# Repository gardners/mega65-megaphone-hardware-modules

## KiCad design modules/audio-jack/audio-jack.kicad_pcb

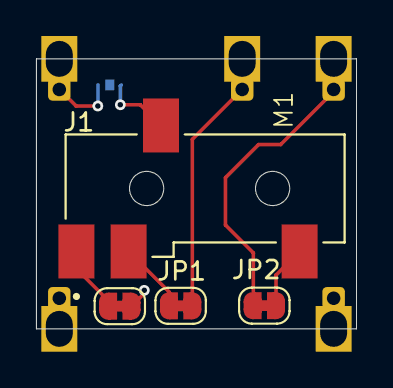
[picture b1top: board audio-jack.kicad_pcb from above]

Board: 2 copper layers, 17.8 x 15.0 mm, 6 parts (1 on the bottom side), 8 nets.

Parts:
J1: SJ-43514-SMT-TR; CUI_SJ-43514-SMT-TR
JP1, JP2, JP3, JP4: Jumper_2_Bridged; SolderJumper-2_P1.3mm_Bridged_RoundedPad1.0x1.5mm
M1: MegaCastle2x7-Module-I15.0x13.0-M8314-SPAREPAD

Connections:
GND: JP3.2 (B), M1.7 (GND)
LEFT: JP4.1 (A), M1.8
MIC: JP1.2 (B), M1.12
unnamed: J1.4, JP1.1 (A)
unnamed: J1.2, JP2.2 (B)
unnamed: J1.1, JP3.1 (A)
unnamed: J1.3, JP4.2 (B)
RIGHT: JP2.1 (A), M1.14

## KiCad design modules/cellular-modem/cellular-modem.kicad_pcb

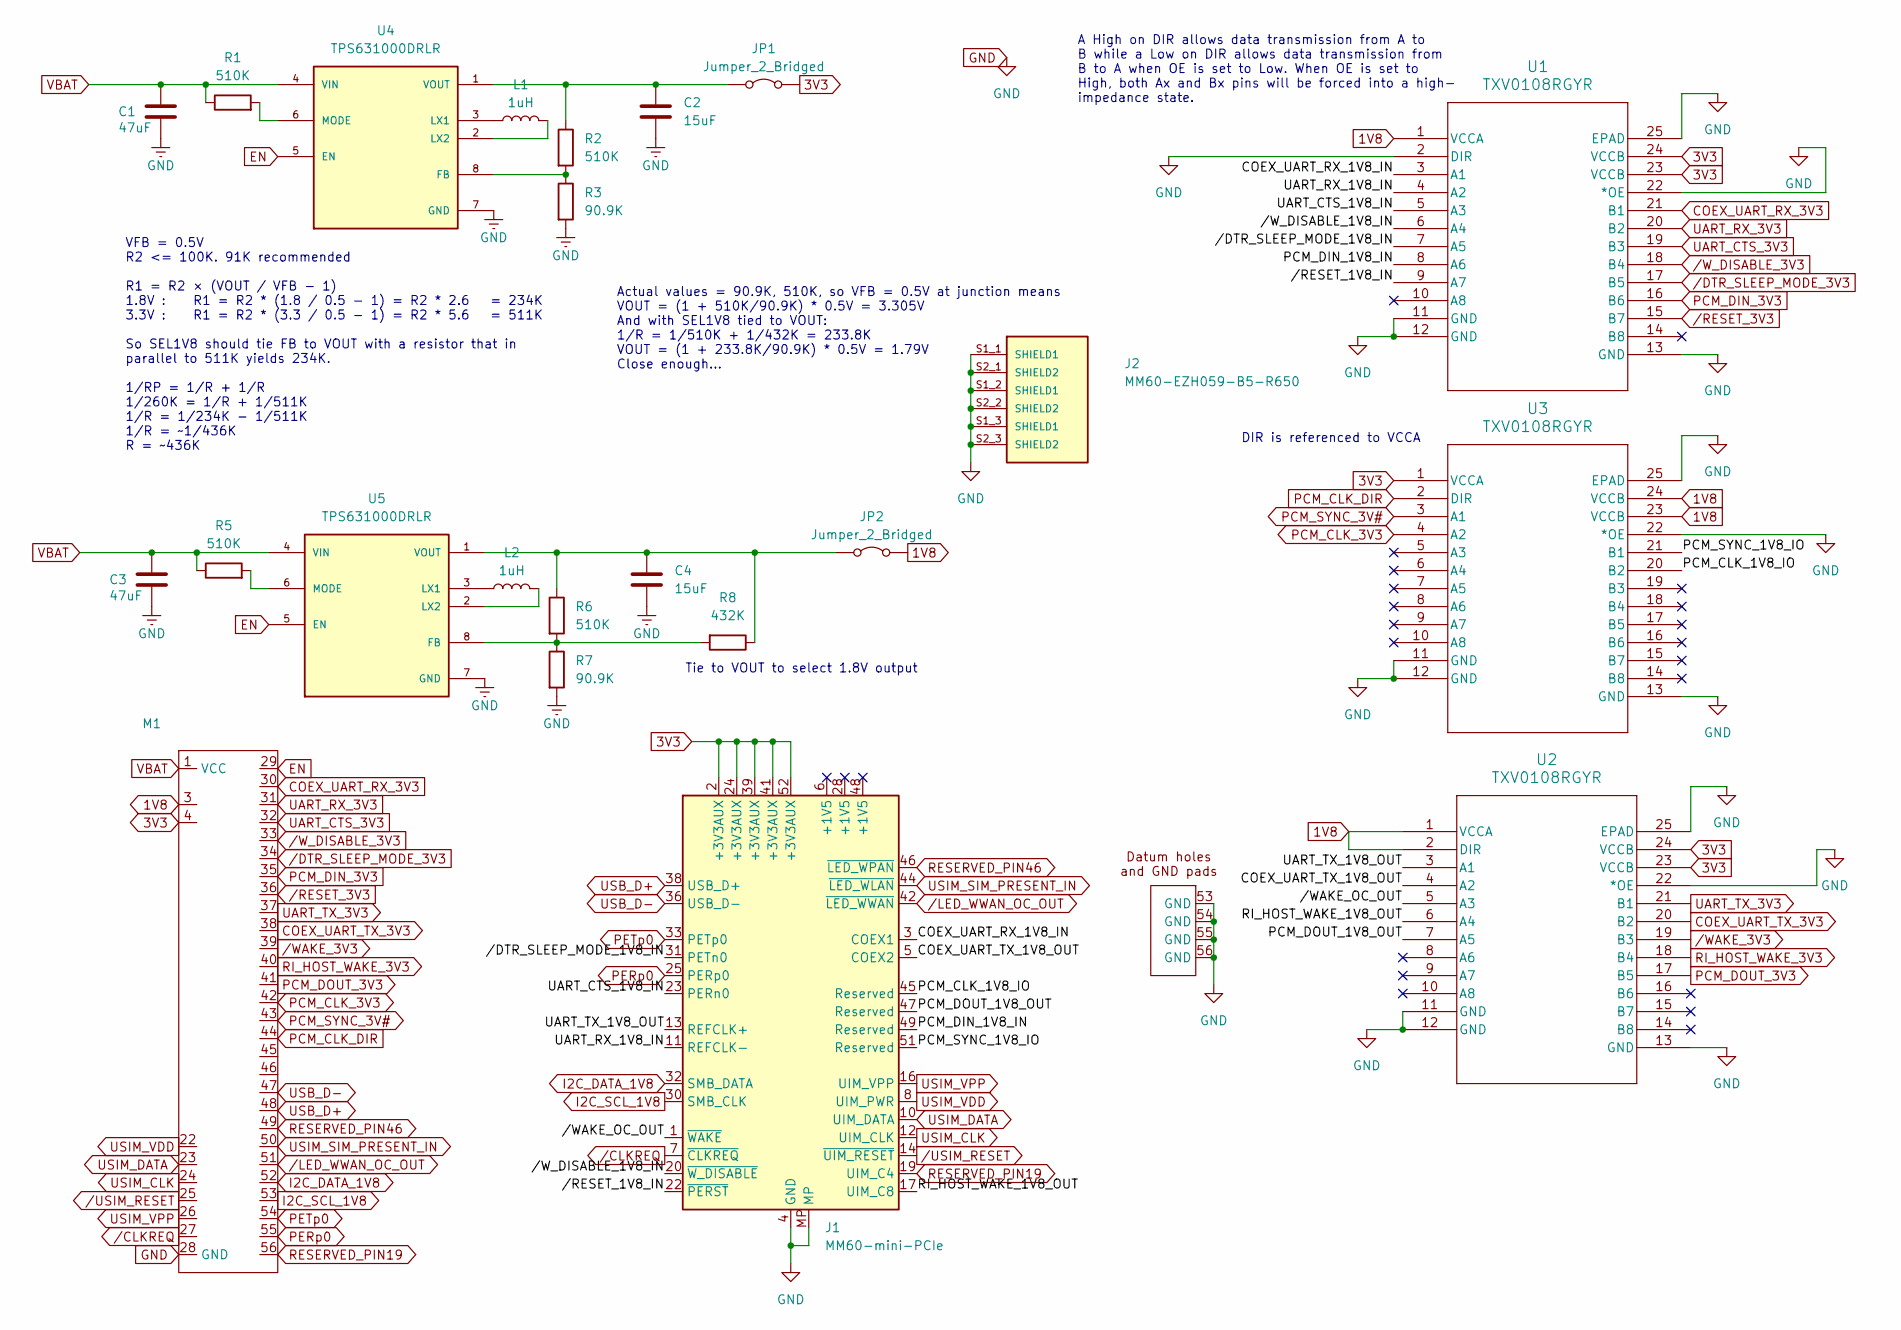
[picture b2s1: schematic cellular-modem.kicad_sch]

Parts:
C1: 47uF; C_0805_2012Metric; Mouser_PN GRM219R60J476ME44
C2, C4: 15uF; C_0805_2012Metric; Mfr. PN C2012X7S1A156M125AC; Mouser_PN 810-C2012X7S1A156M1C
C3: 47uF; C_0805_2012Metric; Mfr. PN GRM219R60J476ME44D; Mouser_PN GRM219R60J476ME44
J1: MM60-mini-PCIe; CONN_MM60-52B1-E1-R650_JAE; Mfr. PN MM60-52B1-G1-R850; Mouser_PN 656-MM6052B1G1R850
J2: MM60-EZH059-B5-R650; JAE_MM60-EZH059-B5-R650; PARTREV 3; Mouser_PN 656-MM60-EZH059-B5-R
JP1, JP2: Jumper_2_Bridged; SolderJumper-2_P1.3mm_Bridged2Bar_RoundedPad1.0x1.5mm
L1: 1uH; L_1008_2520Metric_Pad1.43x2.20mm_HandSolder; Mouser_PN 81-DFE252012P-1R0MP2
L2: 1uH; L_1008_2520Metric_Pad1.43x2.20mm_HandSolder; Mfr. PN DFE252012P-1R0M=P2; Mouser_PN 81-DFE252012P-1R0MP2
M1: MegaCastle2x28-Module-I42.8x66.3-MB00007FFFFFFFF-SPAREPAD
R1, R2, R5, R6: 510K; R_0805_2012Metric; Mouser_PN CR0805-JW-514ELF
R3, R7: 90.9K; R_0805_2012Metric; Mfr. PN RE0805FRE0790K9L; Mouser_PN 603-RE0805FRE0790K9L
R8: 432K; R_0805_2012Metric; Mfr. PN RC0805FR-07432KL; Mouser_PN 603-RC0805FR-07432KL
U1, U2, U3: TXV0108RGYR; VQFN24_RGY_TEX; Mfr. PN TXV0108RGYR; Mouser_PN 595-TXV0108RGYR
U4, U5: TPS631000DRLR; SOT50P160X60-8N; PARTREV B; Mouser_PN 595-TPS631000DRLR

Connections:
1V8: JP2.2 (B), M1.3, U1.1 (VCCA), U2.1 (VCCA), U2.2 (DIR), U3.23 (VCCB), U3.24 (VCCB)
3V3: J1.2 (+3V3AUX), J1.24 (+3V3AUX), J1.39 (+3V3AUX), J1.41 (+3V3AUX), J1.52 (+3V3AUX), JP1.2 (B), M1.4, U1.23 (VCCB), U1.24 (VCCB), U2.23 (VCCB), U2.24 (VCCB), U3.1 (VCCA)
/COEX_UART_RX_1V8_IN: J1.3 (COEX1), U1.3 (A1)
/COEX_UART_TX_1V8_OUT: J1.5 (COEX2), U2.4 (A2)
/PCM_CLK_1V8_IO: J1.45 (Reserved), U3.20 (B2)
/PCM_DIN_1V8_IN: J1.49 (Reserved), U1.8 (A6)
/PCM_DOUT_1V8_OUT: J1.47 (Reserved), U2.7 (A5)
/PCM_SYNC_1V8_IO: J1.51 (Reserved), U3.21 (B1)
/RI_HOST_WAKE_1V8_OUT: J1.17 (UIM_C8), U2.6 (A4)
/UART_CTS_1V8_IN: J1.23 (PERn0), U1.5 (A3)
/UART_RX_1V8_IN: J1.11 (REFCLK-), U1.4 (A2)
/UART_TX_1V8_OUT: J1.13 (REFCLK+), U2.3 (A1)
//DTR_SLEEP_MODE_1V8_IN: J1.31 (PETn0), U1.7 (A5)
//RESET_1V8_IN: J1.22 (~PERST), U1.9 (A7)
//WAKE_OC_OUT: J1.1 (~WAKE), U2.5 (A3)
//W_DISABLE_1V8_IN: J1.20 (~W_DISABLE), U1.6 (A4)
COEX_UART_RX_3V3: M1.30, U1.21 (B1)
COEX_UART_TX_3V3: M1.38, U2.20 (B2)
EN: M1.29, U4.5 (EN), U5.5 (EN)
GND: C1.1, C2.2, C3.1, C4.2, J1.4 (GND), J1.9 (GND), J1.15 (GND), J1.18 (GND), J1.21 (GND), J1.26 (GND), J1.27 (GND), J1.29 (GND), J1.34 (GND), J1.35 (GND), J1.37 (GND), J1.40 (GND), J1.43 (GND), J1.50 (GND), J1.53 (GND), J1.54 (GND), J1.55 (GND), J1.56 (GND), J1.MP, J2.S1_1 (SHIELD1), J2.S1_2 (SHIELD1), J2.S1_3 (SHIELD1), J2.S2_1 (SHIELD2), J2.S2_2 (SHIELD2), J2.S2_3 (SHIELD2), M1.28 (GND), R3.2, R7.2, U1.2 (DIR), U1.11 (GND), U1.12 (GND), U1.13 (GND), U1.22 (*OE), U1.25 (EPAD), U2.11 (GND), U2.12 (GND), U2.13 (GND), U2.22 (*OE), U2.25 (EPAD), U3.11 (GND), U3.12 (GND), U3.13 (GND), U3.22 (*OE), U3.25 (EPAD), U4.7 (GND), U5.7 (GND)
I2C_DATA_1V8: J1.32 (SMB_DATA), M1.52
I2C_SCL_1V8: J1.30 (SMB_CLK), M1.53
unnamed: C2.1, JP1.1 (A), R2.1, U4.1 (VOUT)
unnamed: C4.1, JP2.1 (A), R6.1, R8.1, U5.1 (VOUT)
unnamed: R2.2, R3.1, U4.8 (FB)
unnamed: L1.1, U4.3 (LX1)
unnamed: L1.2, U4.2 (LX2)
unnamed: R1.2, U4.6 (MODE)
unnamed: R6.2, R7.1, R8.2, U5.8 (FB)
unnamed: L2.1, U5.3 (LX1)
unnamed: L2.2, U5.2 (LX2)
unnamed: R5.2, U5.6 (MODE)
PCM_CLK_3V3: M1.42, U3.4 (A2)
PCM_CLK_DIR: M1.44, U3.2 (DIR)
PCM_DIN_3V3: M1.35, U1.16 (B6)
PCM_DOUT_3V3: M1.41, U2.17 (B5)
PCM_SYNC_3V#: M1.43, U3.3 (A1)
PERp0: J1.25 (PERp0), M1.55
PETp0: J1.33 (PETp0), M1.54
RESERVED_PIN19: J1.19 (UIM_C4), M1.56
RESERVED_PIN46: J1.46 (~LED_WPAN), M1.49
RI_HOST_WAKE_3V3: M1.40, U2.18 (B4)
UART_CTS_3V3: M1.32, U1.19 (B3)
UART_RX_3V3: M1.31, U1.20 (B2)
UART_TX_3V3: M1.37, U2.21 (B1)
USB_D+: J1.38 (USB_D+), M1.48
USB_D-: J1.36 (USB_D-), M1.47
USIM_CLK: J1.12 (UIM_CLK), M1.24
USIM_DATA: J1.10 (UIM_DATA), M1.23
USIM_SIM_PRESENT_IN: J1.44 (~LED_WLAN), M1.50
USIM_VDD: J1.8 (UIM_PWR), M1.22
USIM_VPP: J1.16 (UIM_VPP), M1.26
VBAT: C1.2, C3.2, M1.1 (VCC), R1.1, R5.1, U4.4 (VIN), U5.4 (VIN)
/CLKREQ: J1.7 (~CLKREQ), M1.27
/DTR_SLEEP_MODE_3V3: M1.34, U1.17 (B5)
/LED_WWAN_OC_OUT: J1.42 (~LED_WWAN), M1.51
/RESET_3V3: M1.36, U1.15 (B7)
/USIM_RESET: J1.14 (~UIM_RESET), M1.25
/WAKE_3V3: M1.39, U2.19 (B3)
/W_DISABLE_3V3: M1.33, U1.18 (B4)

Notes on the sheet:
Tie to VOUT to select 1.8V output
Actual values = 90.9K, 510K, so VFB = 0.5V at junction means VOUT = (1 + 510K/90.9K) * 0.5V = 3.305V And with SEL1V8 tied to VOUT: 1/R = 1/510K + 1/432K = 233.8K VOUT = (1 + 233.8K/90.9K) * 0.5V = 1.79V Close enough...
VFB = 0.5V R2 <= 100K. 91K recommended R1 = R2 × (VOUT / VFB - 1) 1.8V : R1 = R2 * (1.8 / 0.5 - 1) = R2 * 2.6 = 234K 3.3V : R1 = R2 * (3.3 / 0.5 - 1) = R2 * 5.6 = 511K So SEL1V8 should tie FB to VOUT with a resistor that in parallel to 511K yields 234K. 1/RP = 1/R + 1/R 1/260K = 1/R + 1/511K 1/R = 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
DIR is referenced to VCCA
A High on DIR allows data transmission from A to B while a Low on DIR allows data transmission from B to A when OE is set to Low. When OE is set to High, both Ax and Bx pins will be forced into a high- impedance state.

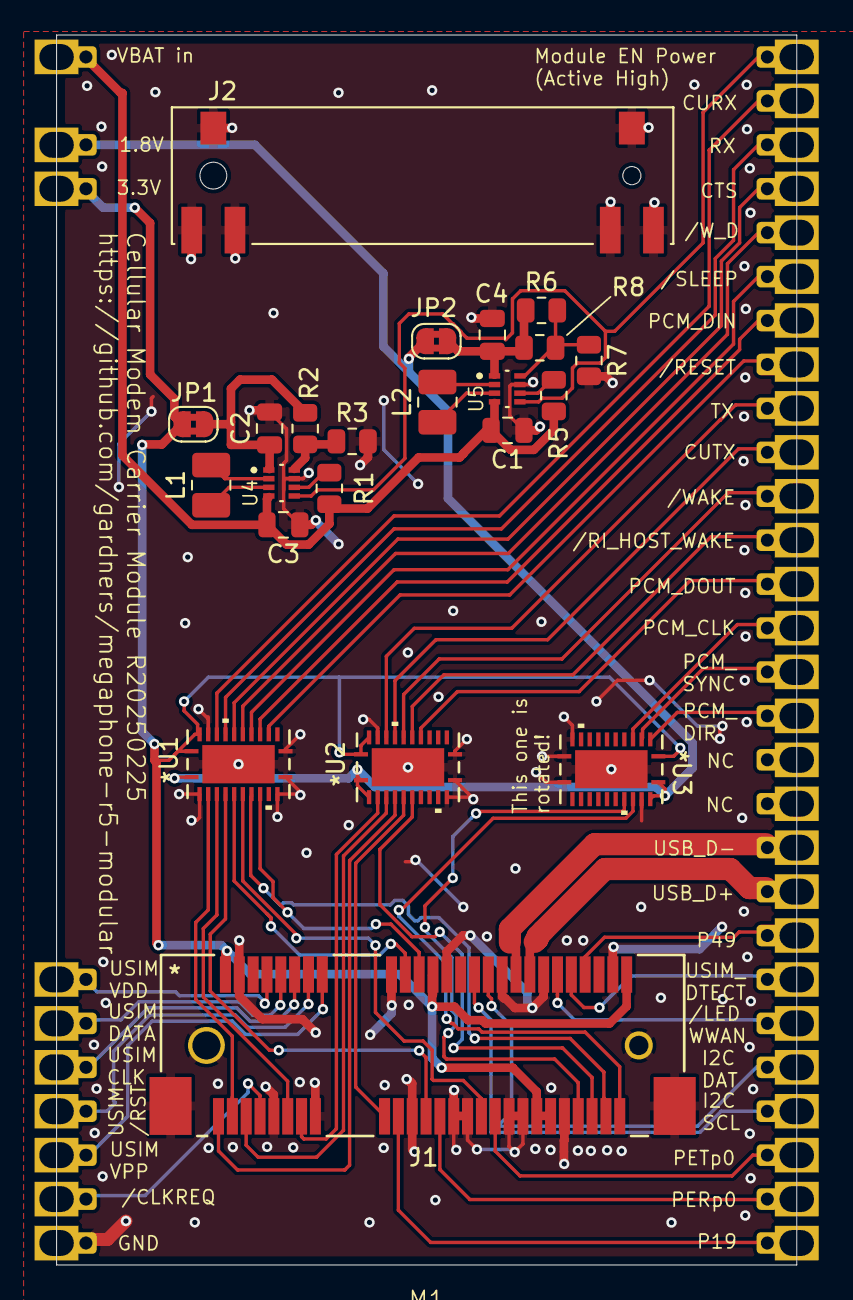
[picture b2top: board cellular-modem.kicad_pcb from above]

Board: 4 copper layers, 42.8 x 71.1 mm, 23 parts (0 on the bottom side), 60 nets.

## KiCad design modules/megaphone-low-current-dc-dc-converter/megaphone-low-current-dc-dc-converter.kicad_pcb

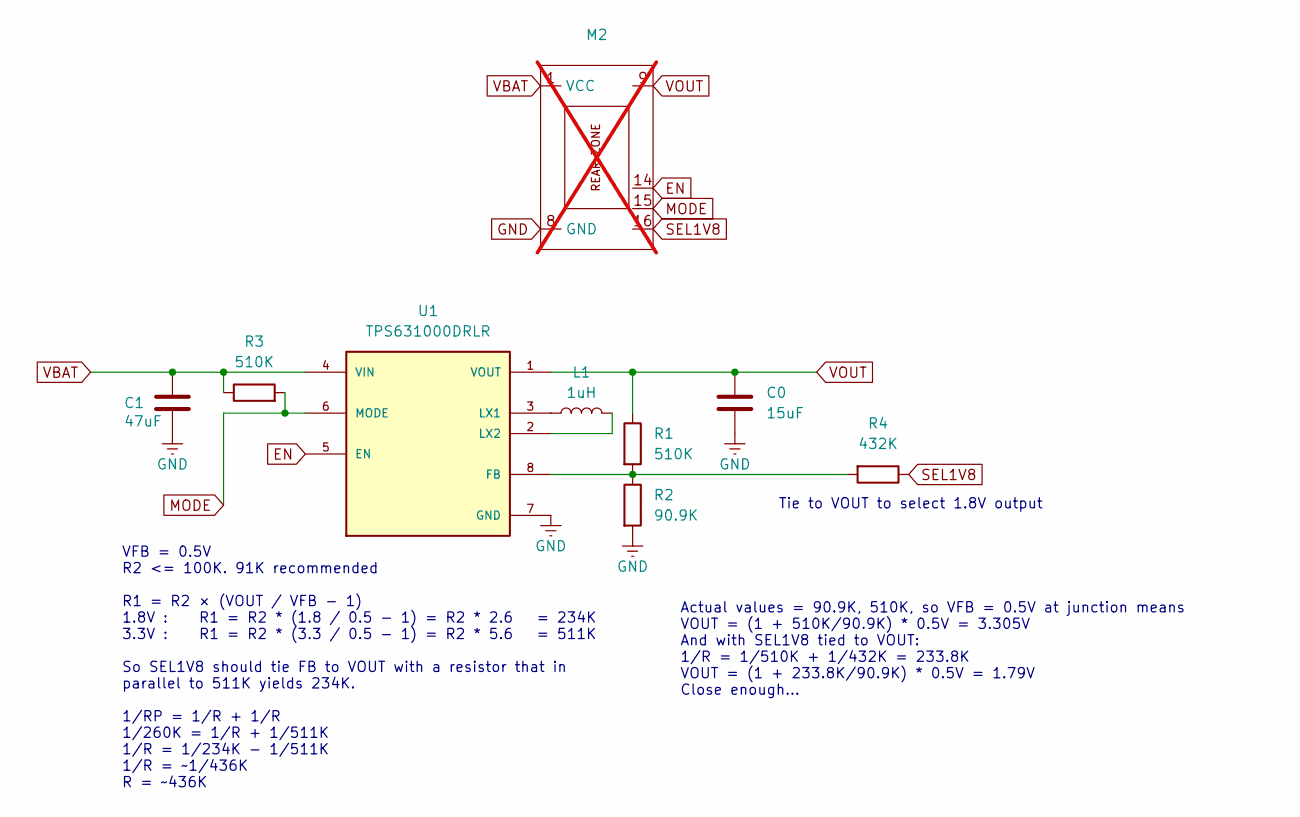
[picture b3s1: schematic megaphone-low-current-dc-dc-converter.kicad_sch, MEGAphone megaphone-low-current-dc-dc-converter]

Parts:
C0: 15uF; C_0805_2012Metric; LCSC C23692982
C1: 47uF; C_0805_2012Metric; LCSC C16780
L1: 1uH; L_1008_2520Metric_Pad1.43x2.20mm_HandSolder; LCSC C882955
M2: MegaCastle2x8-Module-I15.0x15.5-M8187-SPAREPAD; not fitted
R1, R3: 510K; R_0805_2012Metric; LCSC C2907332
R2: 90.9K; R_0805_2012Metric; LCSC C229044
R4: 432K; R_0805_2012Metric; LCSC C137526
U1: TPS631000DRLR; SOT50P160X60-8N; PARTREV B; LCSC C5219190

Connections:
EN: M2.14, U1.5 (EN)
GND: C0.2, C1.1, M2.8 (GND), R2.2, U1.7 (GND)
MODE: M2.15, R3.2, U1.6 (MODE)
unnamed: R1.2, R2.1, R4.2, U1.8 (FB)
unnamed: L1.1, U1.3 (LX1)
unnamed: L1.2, U1.2 (LX2)
SEL1V8: M2.16, R4.1
VBAT: C1.2, M2.1 (VCC), R3.1, U1.4 (VIN)
VOUT: C0.1, M2.9, R1.1, U1.1 (VOUT)

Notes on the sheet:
VFB = 0.5V R2 <= 100K. 91K recommended R1 = R2 × (VOUT / VFB - 1) 1.8V : R1 = R2 * (1.8 / 0.5 - 1) = R2 * 2.6 = 234K 3.3V : R1 = R2 * (3.3 / 0.5 - 1) = R2 * 5.6 = 511K So SEL1V8 should tie FB to VOUT with a resistor that in parallel to 511K yields 234K. 1/RP = 1/R + 1/R 1/260K = 1/R + 1/511K 1/R = 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
Actual values = 90.9K, 510K, so VFB = 0.5V at junction means VOUT = (1 + 510K/90.9K) * 0.5V = 3.305V And with SEL1V8 tied to VOUT: 1/R = 1/510K + 1/432K = 233.8K VOUT = (1 + 233.8K/90.9K) * 0.5V = 1.79V Close enough...
Tie to VOUT to select 1.8V output

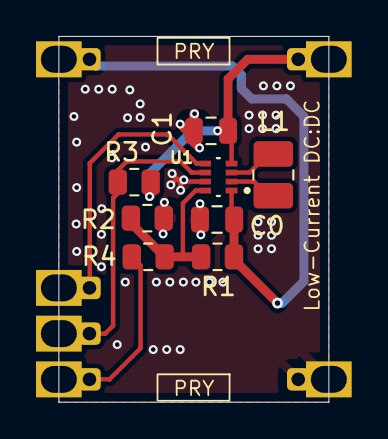
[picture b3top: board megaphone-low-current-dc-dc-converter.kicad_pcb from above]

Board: 2 copper layers, 15.0 x 20.3 mm, 9 parts (1 on the bottom side), 9 nets.

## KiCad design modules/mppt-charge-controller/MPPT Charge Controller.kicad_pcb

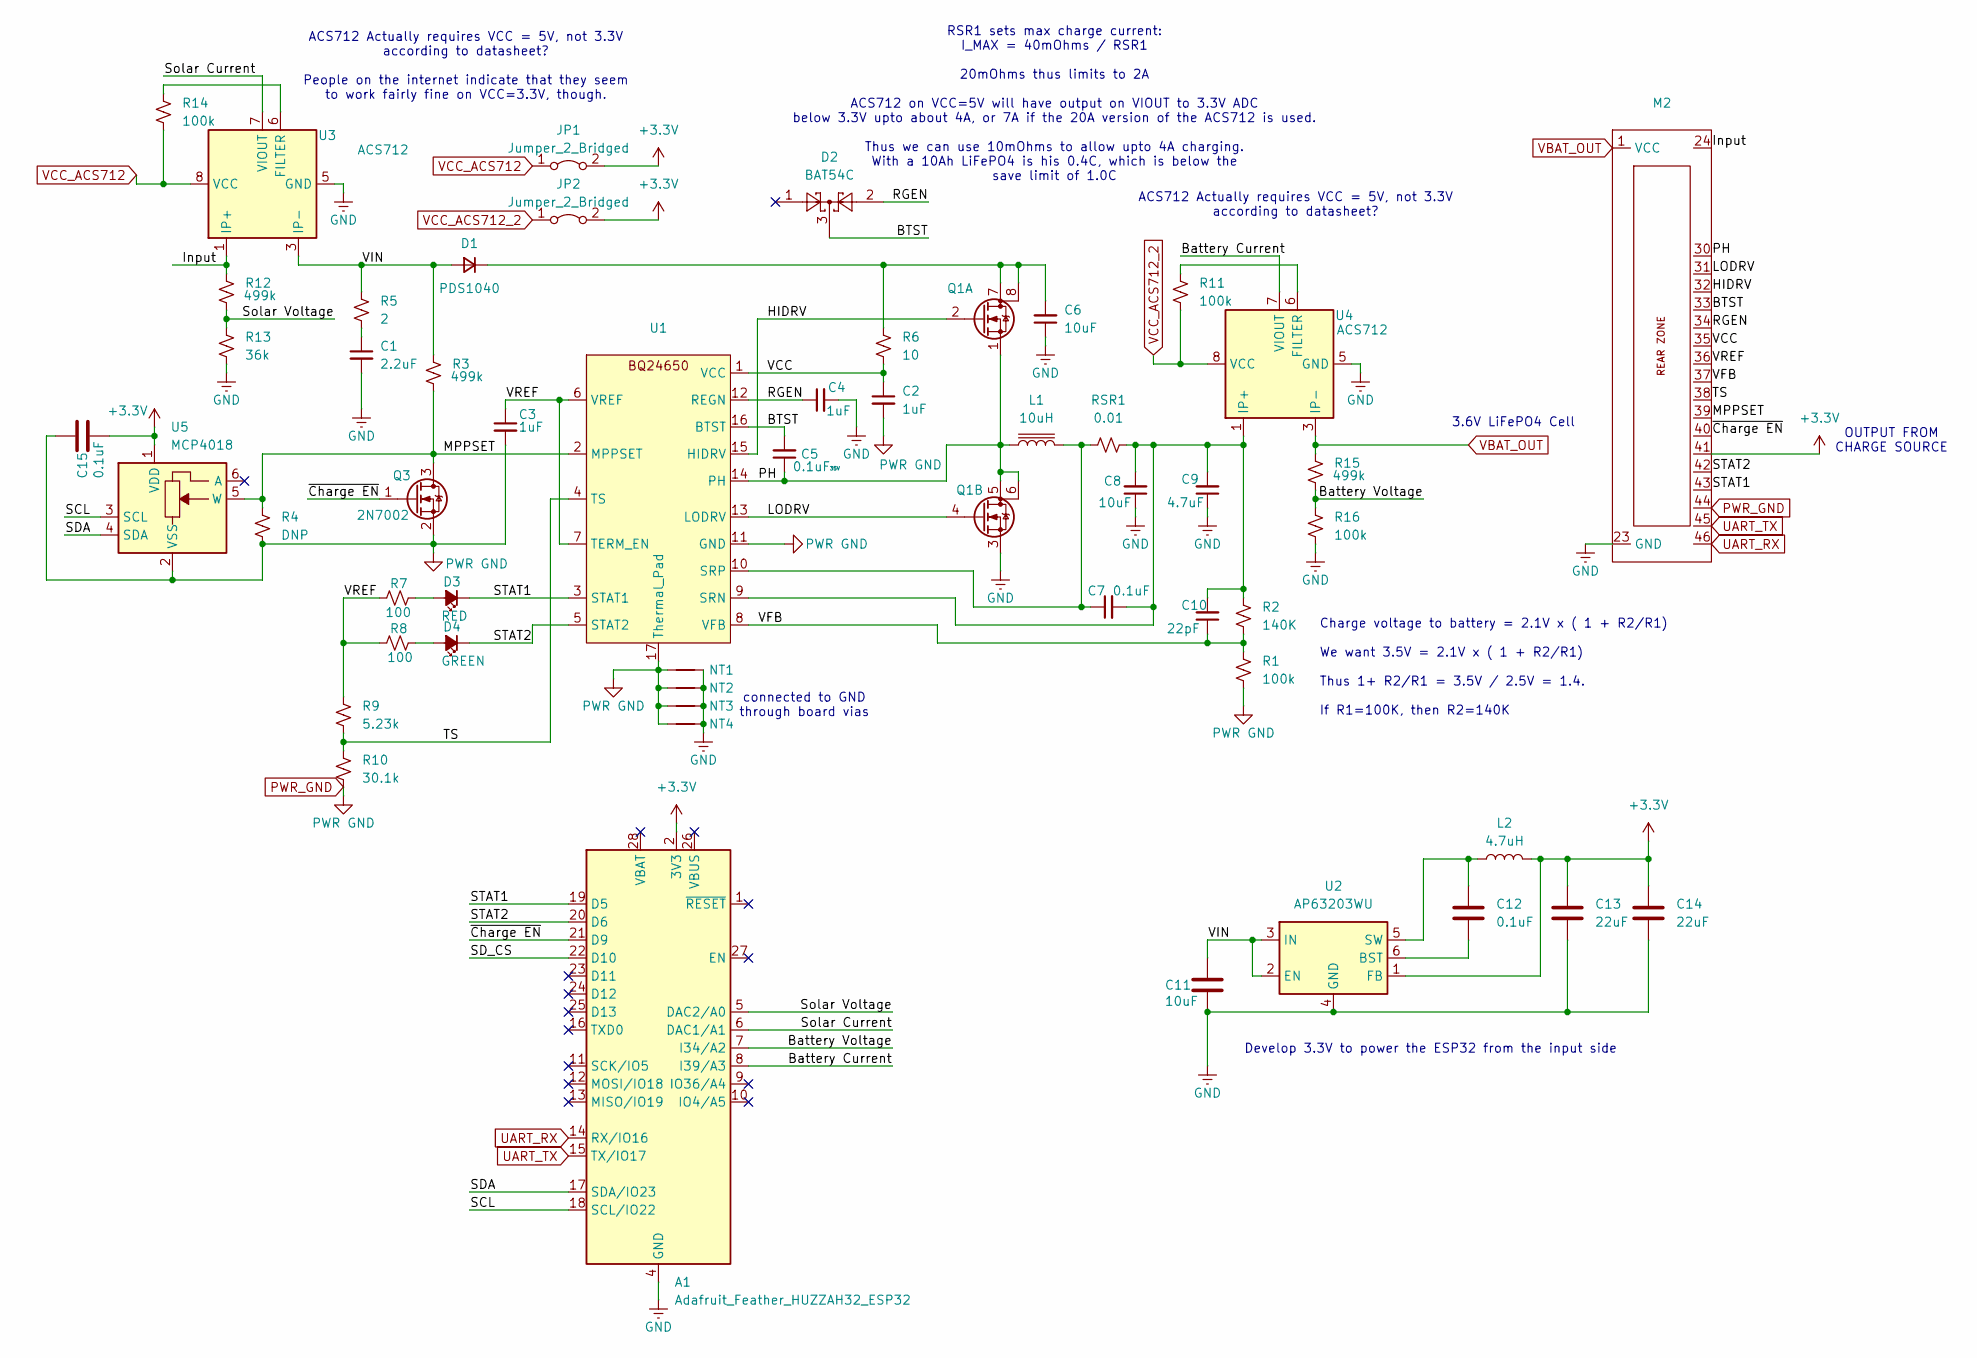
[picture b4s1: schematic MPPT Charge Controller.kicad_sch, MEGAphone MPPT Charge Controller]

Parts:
A1: Adafruit_Feather_HUZZAH32_ESP32; Adafruit_Feather
C1: 2.2uF; C_1210_3225Metric
C2, C3, C4: 1uF; C_0603_1608Metric
C5: 0.1uF; C_0603_1608Metric; Voltage Rating 35V
C6, C8: 10uF; C_1206_3216Metric
C7, C12, C15: 0.1uF; C_0603_1608Metric
C9: 4.7uF; C_0805_2012Metric
C10: 22pF; C_0603_1608Metric
C11: 10uF; C_0603_1608Metric
C13, C14: 22uF; C_0603_1608Metric
D1: PDS1040; D_PowerDI-5
D2: BAT54C; SOT-23
D3: RED; LED_0603_1608Metric
D4: GREEN; LED_0603_1608Metric
JP1, JP2: Jumper_2_Bridged; SolderJumper-2_P1.3mm_Bridged_RoundedPad1.0x1.5mm
L1: 10uH; L_Vishay_6.9x6.5
L2: 4.7uH; L_Vishay_IFSC-1515AH_4x4x1.8mm
M2: MegaCastle2x23-Module-I30.0x53.6-M80000307FFFC-PANEL
NT1, NT2, NT3, NT4: NetTie-2_SMD_Pad0.5mm
Q1: SI7272DP; PowerPAK_SO-8_Dual
Q3: 2N7002; SOT-23
R1, R11, R14, R16: 100k; R_0603_1608Metric
R2: 140K; R_0603_1608Metric
R3, R12, R15: 499k; R_0603_1608Metric
R4: DNP; R_0603_1608Metric
R5: 2; R_2512_6332Metric
R6: 10; R_0603_1608Metric
R7, R8: 100; R_0603_1608Metric
R9: 5.23k; R_0603_1608Metric
R10: 30.1k; R_0603_1608Metric
R13: 36k; R_0603_1608Metric
RSR1: 0.01; R_1206_3216Metric
U1: VQFN-16_EP_3.5x3.5_Pitch0.5mm
U2: AP63203WU; TSOT-23-6
U3, U4: ACS712; SOIC-8_3.9x4.9mm_P1.27mm
U5: MCP4018; SOT-363_SC-70-6

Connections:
+3.3V: A1.2 (3V3), C13.1, C14.1, C15.1, JP1.2 (B), JP2.2 (B), L2.2, M2.41, U2.1 (FB), U5.1 (VDD)
/BTST: C5.2, D2.3, M2.33, U1.16 (BTST)
/Battery Current: A1.8 (I39/A3), U4.7 (VIOUT)
/Battery Voltage: A1.7 (I34/A2), R15.2, R16.1
/HIDRV: M2.32, Q1.2 (G), U1.15 (HIDRV)
/Input: M2.24, R12.1, U3.1 (IP+), U3.2 (IP+)
/LODRV: M2.31, Q1.4 (G), U1.13 (LODRV)
/MPPSET: M2.39, Q3.3 (D), R3.2, R4.1, U1.2 (MPPSET), U5.5 (W)
/PH: C5.1, L1.1, M2.30, Q1.1 (S), Q1.5 (D), Q1.6 (D), U1.14 (PH)
/RGEN: C4.1, D2.2, M2.34, U1.12 (REGN)
/SCL: A1.18 (SCL/IO22), U5.3 (SCL)
/SDA: A1.17 (SDA/IO23), U5.4 (SDA)
/SD_CS: A1.22 (D10)
/STAT1: A1.19 (D5), D3.1 (K), M2.43, U1.3 (STAT1)
/STAT2: A1.20 (D6), D4.1 (K), M2.42, U1.5 (STAT2)
/Solar Current: A1.6 (DAC1/A1), U3.7 (VIOUT)
/Solar Voltage: A1.5 (DAC2/A0), R12.2, R13.1
/TS: M2.38, R9.2, R10.1, U1.4 (TS)
/VCC: C2.1, M2.35, R6.2, U1.1 (VCC)
/VFB: C10.1, M2.37, R1.1, R2.2, U1.8 (VFB)
/VIN: C11.2, D1.2 (A), R3.1, R5.1, U2.2 (EN), U2.3 (IN), U3.3 (IP-), U3.4 (IP-)
/VREF: C3.1, M2.36, R7.1, R8.1, R9.1, U1.6 (VREF), U1.7 (TERM_EN)
/~Charge EN: A1.21 (D9), M2.40, Q3.1 (G)
GND: A1.4 (GND), C1.2, C4.2, C6.1, C8.1, C9.1, C11.1, C13.2, C14.2, M2.23 (GND), NT1.2, NT2.2, NT3.2, NT4.2, Q1.3 (S), R13.2, R16.2, U2.4 (GND), U3.5 (GND), U4.5 (GND)
unnamed: C1.1, R5.2
unnamed: C6.2, D1.1 (K), Q1.7 (D), Q1.8 (D), R6.1
unnamed: D3.2 (A), R7.2
unnamed: D4.2 (A), R8.2
unnamed: C7.2, C8.2, C9.2, C10.2, R2.1, RSR1.1, U1.9 (SRN), U4.1 (IP+), U4.2 (IP+)
unnamed: C7.1, L1.2, RSR1.2, U1.10 (SRP)
unnamed: C12.2, U2.6 (BST)
unnamed: C12.1, L2.1, U2.5 (SW)
unnamed: R14.1, U3.6 (FILTER)
unnamed: R11.1, U4.6 (FILTER)
PWR_GND: C2.2, C3.2, C15.2, M2.44, NT1.1, NT2.1, NT3.1, NT4.1, Q3.2 (S), R1.2, R4.2, R10.2, U1.11 (GND), U1.17 (Thermal_Pad), U5.2 (VSS)
UART_RX: A1.14 (RX/IO16), M2.46
UART_TX: A1.15 (TX/IO17), M2.45
VBAT_OUT: M2.1 (VCC), R15.1, U4.3 (IP-), U4.4 (IP-)
VCC_ACS712: JP1.1 (A), R14.2, U3.8 (VCC)
VCC_ACS712_2: JP2.1 (A), R11.2, U4.8 (VCC)

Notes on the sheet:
ACS712 Actually requires VCC = 5V, not 3.3V according to datasheet?
ACS712 Actually requires VCC = 5V, not 3.3V according to datasheet? People on the internet indicate that they seem to work fairly fine on VCC=3.3V, though.
3.6V LiFePO4 Cell
OUTPUT FROM CHARGE SOURCE
Charge voltage to battery = 2.1V x ( 1 + R2/R1) We want 3.5V = 2.1V x ( 1 + R2/R1) Thus 1+ R2/R1 = 3.5V / 2.5V = 1.4. If R1=100K, then R2=140K
RSR1 sets max charge current: I_MAX = 40mOhms / RSR1 20mOhms thus limits to 2A ACS712 on VCC=5V will have output on VIOUT to 3.3V ADC below 3.3V upto about 4A, or 7A if the 20A version of the ACS712 is used. Thus we can use 10mOhms to allow upto 4A charging. With a 10Ah LiFePO4 is his 0.4C, which i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
connected to GND through board vias
Develop 3.3V to power the ESP32 from the input side

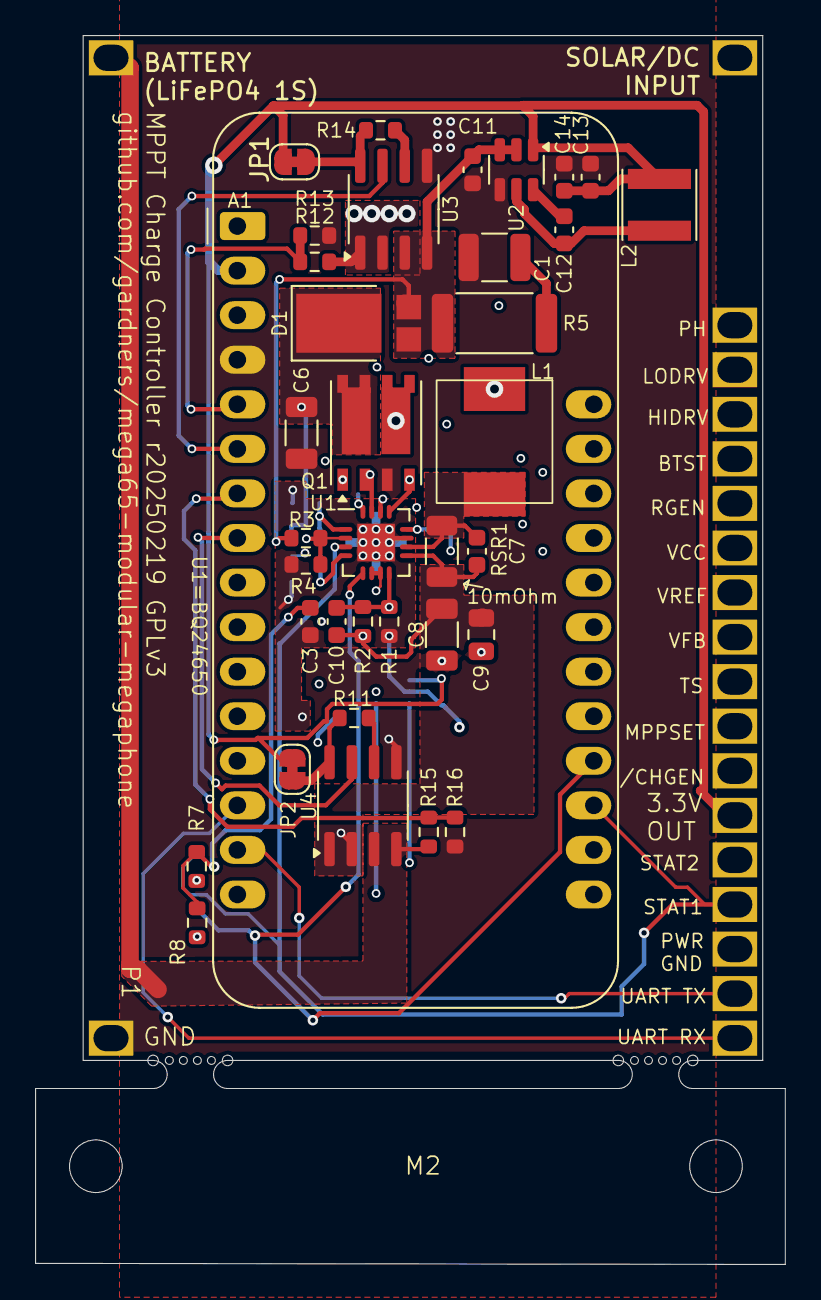
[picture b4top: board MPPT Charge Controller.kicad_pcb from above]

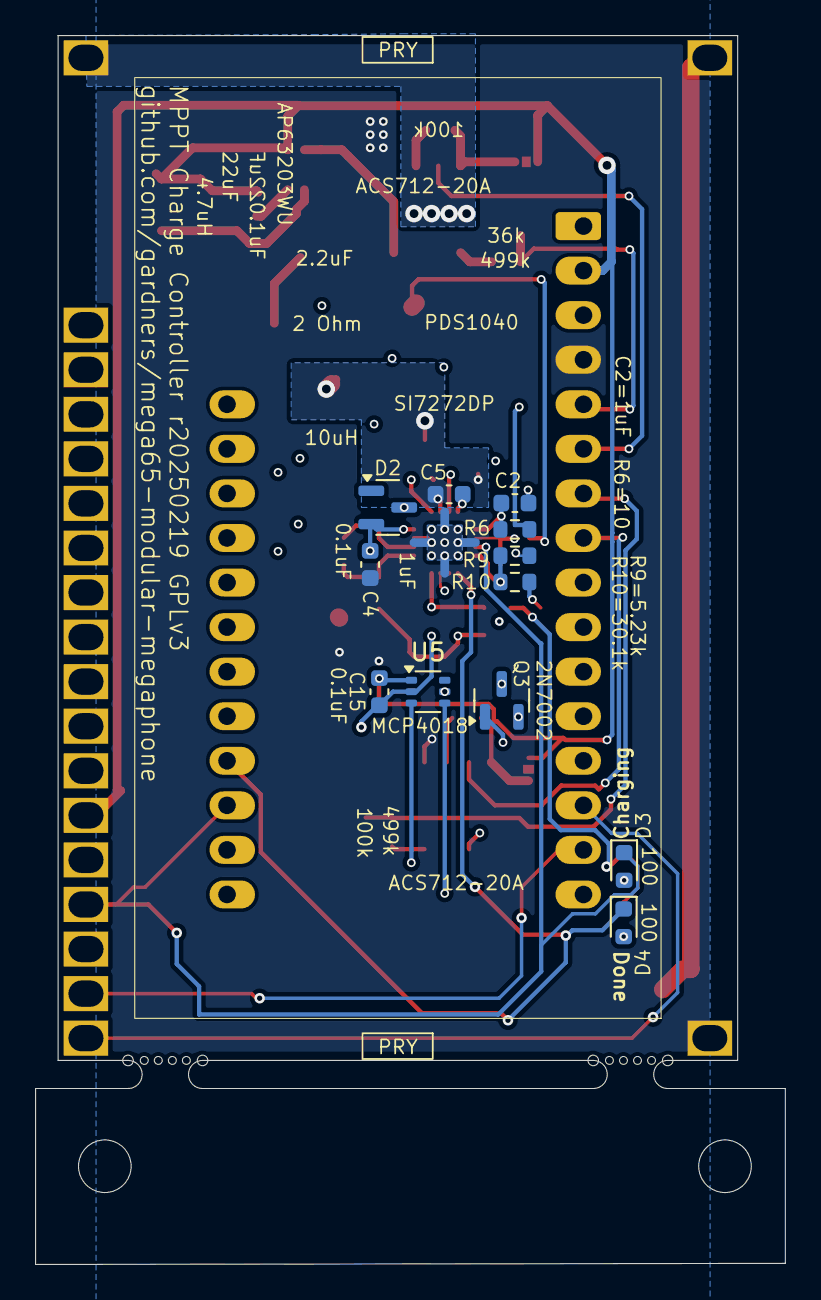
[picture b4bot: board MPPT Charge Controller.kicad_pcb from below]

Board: 4 copper layers, 42.7 x 70.0 mm, 53 parts (16 on the bottom side), 39 nets.

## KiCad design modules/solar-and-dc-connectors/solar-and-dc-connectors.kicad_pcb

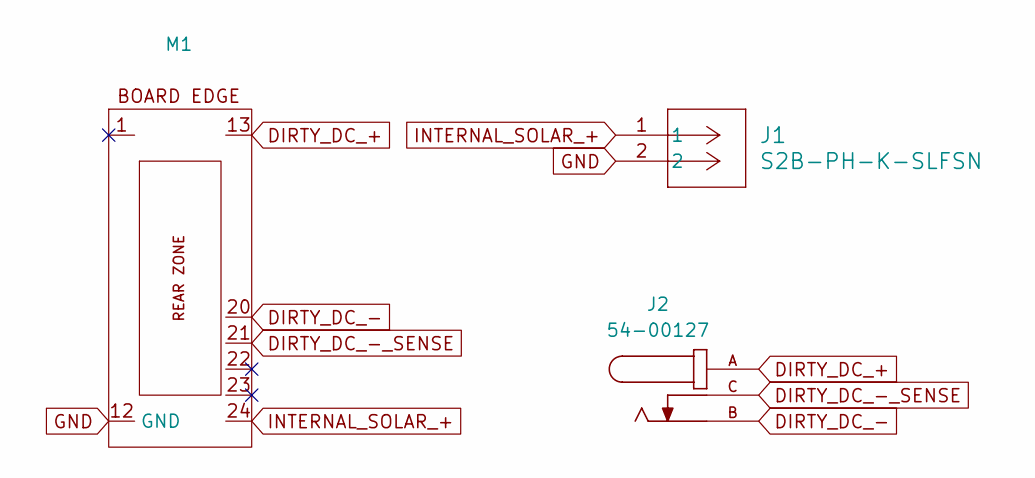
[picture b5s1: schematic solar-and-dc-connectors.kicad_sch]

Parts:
J1: S2B-PH-K-SLFSN; CONN_S2B-PH-K-S_JST; Mouser PN 306-S2BPHKSLFSNPP
J2: 54-00127; TENSILITY_54-00127; PARTREV A
M1: MegaCastle2x12-Module-I20.0x25.7-M80181F-SPAREPAD

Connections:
DIRTY_DC_+: J2.A, M1.13
DIRTY_DC_-: J2.B, M1.20
DIRTY_DC_-_SENSE: J2.C, M1.21
GND: J1.2, M1.12 (GND)
INTERNAL_SOLAR_+: J1.1, M1.24

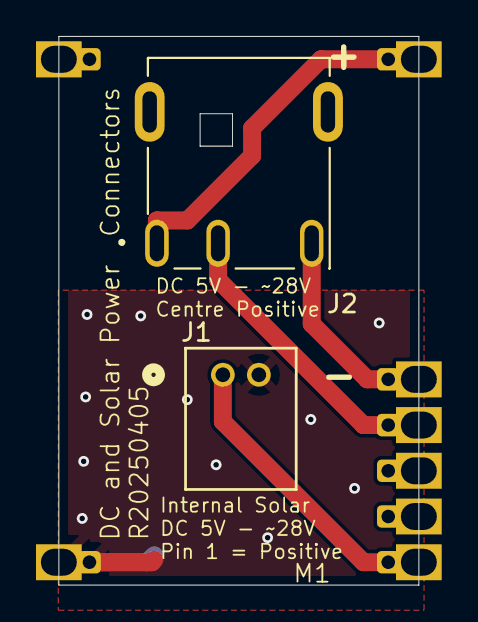
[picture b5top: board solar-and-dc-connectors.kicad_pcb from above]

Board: 2 copper layers, 20.0 x 30.5 mm, 3 parts (0 on the bottom side), 5 nets.

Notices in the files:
modules/mppt-charge-controller/MPPT Charge Controller.kicad_pcb:
${TITLE} r20250219 GPLv3
